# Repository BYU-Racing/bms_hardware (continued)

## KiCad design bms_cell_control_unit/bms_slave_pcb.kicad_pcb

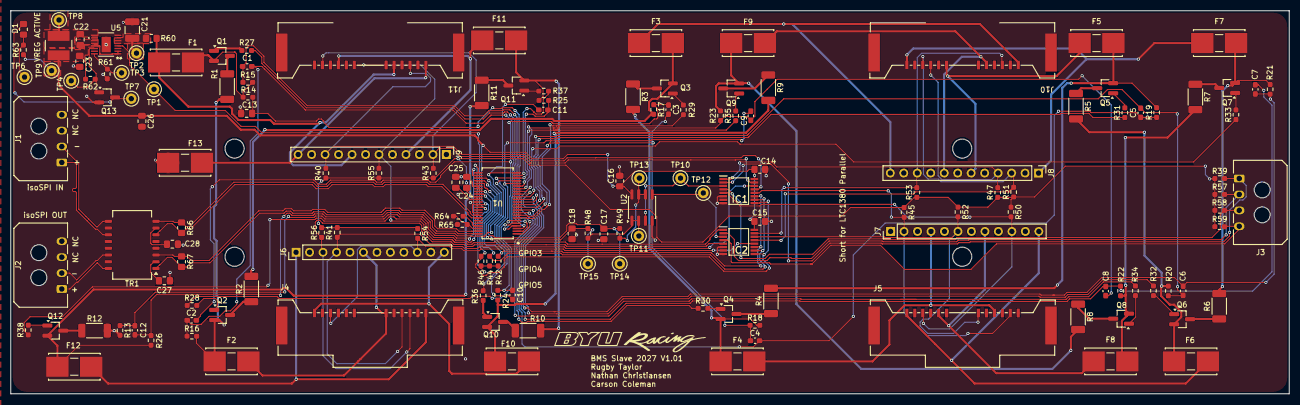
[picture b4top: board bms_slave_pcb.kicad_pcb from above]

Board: 2 copper layers, 241.0 x 72.2 mm, 152 parts (0 on the bottom side), 124 nets.

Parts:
C1, C2, C3, C4, C5, C6, C7, C8, C9, C10, C11, C12: 10nF; C_0603_1608Metric_Pad1.08x0.95mm_HandSolder
C13: 100nF; C_0805_2012Metric_Pad1.18x1.45mm_HandSolder
C14: 1uF; R_0805_2012Metric_Pad1.20x1.40mm_HandSolder
C15, C16: 1uf; R_0805_2012Metric_Pad1.20x1.40mm_HandSolder
C17, C18: 10nF; R_0805_2012Metric_Pad1.20x1.40mm_HandSolder
C21: 2.2uF; C_1210_3225Metric_Pad1.33x2.70mm_HandSolder
C22, C23: 22uF; C_0805_2012Metric_Pad1.18x1.45mm_HandSolder
C24, C25, C26: 1uF; C_0805_2012Metric_Pad1.18x1.45mm_HandSolder
C27, C28: 10nF; C_0805_2012Metric_Pad1.18x1.45mm_HandSolder
D1: LED; R_0805_2012Metric_Pad1.20x1.40mm_HandSolder
F1, F13: 500mA; Littelfuse_01550900M_Fuse_Blok_Cartridge
F2, F3, F4, F5, F6, F7, F8, F9, F10, F11, F12: 250mA; Littelfuse_01550900M_Fuse_Blok_Cartridge
IC1, IC2: TMUX1308AQPWRQ1; SOP65P640X120-16N
J1: isoSPI Daisy Chain IN; Molex_Micro-Fit_3.0_43650-0400_1x04_P3.00mm_Horizontal
J2: isoSPI Daisy Chain OUT; Molex_Micro-Fit_3.0_43650-0400_1x04_P3.00mm_Horizontal
J3: Extra Thermistor Connector; Molex_Micro-Fit_3.0_43650-0400_1x04_P3.00mm_Horizontal
J4: Module Top Left FPC Female; FPC_Female_Connector
J5: Module Top Right FPC Female; FPC_Female_Connector
J6, J7, J8, J9: Breadboard pins for testing; PinHeader_1x12_P2.54mm_Vertical
J10: Module Bottom Left FPC Female; FPC_Female_Connector
J11: Module Bottom Right FPC Female; FPC_Female_Connector
L1: 33uH; IND_LQH5BPH330MT0L
Q1, Q2, Q3, Q4, Q5, Q6, Q7, Q8, Q9, Q10, Q11, Q12: BSS308PE; SOT-23_Handsoldering
Q13: 2N7002; SOT-23_Handsoldering
R1, R2, R3, R4, R5, R6, R7, R8, R9, R10, R11, R12: 33; R_2010_5025Metric_Pad1.40x2.65mm_HandSolder
R13, R14, R15, R16, R17, R18, R19, R20, R21, R22, R23, R24, R25, R26, R48, R49: 100; R_0603_1608Metric_Pad0.98x0.95mm_HandSolder
R27, R28, R29, R30, R31, R32, R33, R34, R35, R36, R37, R38: 3.3k; R_0603_1608Metric_Pad0.98x0.95mm_HandSolder
R39, R40, R41, R43, R45, R47, R50, R51, R52, R53, R54, R55, R56, R57, R58, R59: 10k; R_0603_1608Metric_Pad0.98x0.95mm_HandSolder
R42, R44, R46: 4.7K; R_0603_1608Metric_Pad0.98x0.95mm_HandSolder
R60: 470; R_0805_2012Metric_Pad1.20x1.40mm_HandSolder
R61: 374k; R_0603_1608Metric_Pad0.98x0.95mm_HandSolder
R62: 220k; R_0603_1608Metric_Pad0.98x0.95mm_HandSolder
R63: 2.2k; R_0603_1608Metric_Pad0.98x0.95mm_HandSolder
R64, R65: 1k; R_0603_1608Metric_Pad0.98x0.95mm_HandSolder
R66, R67: 100; R_0805_2012Metric_Pad1.20x1.40mm_HandSolder
TP1, TP2, TP3, TP4, TP6, TP7, TP8, TP9, TP10, TP11, TP12, TP13, TP14, TP15: TestPoint; TestPoint_Keystone_5000-5004_Miniature
TR1: TG110I-AE050N5xx; Transformer_Ethernet_Halo_N5_SO-16_7.11x12.7mm
U1: LTC6811HGI-1I-3ZZTRPBF; 05-08-1887_ADI
U2: TLV9002IDR; SOIC-8_3.9x4.9mm_P1.27mm
U5: LT3990HMSEI-5I-PBF; MSOP-16_MSE_LIT

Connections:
/FPC Connections/TH1: IC1.13 (S0), J9.10, J11.10, R40.2
/FPC Connections/TH2: IC1.14 (S1), J4.4, J6.4, R41.2
/FPC Connections/TH3: IC1.15 (S2), J9.2, J11.2, R43.2
/FPC Connections/TH4: IC1.12 (S3), J5.2, J7.2, R45.2
/FPC Connections/TH5: IC1.1 (S4), J8.4, J10.4, R47.2
/FPC Connections/TH6: IC1.5 (S5), J5.10, J7.10, R50.2
/FPC Connections/TH7: IC2.13 (S0), J8.3, J10.3, R51.2
/FPC Connections/TH8: IC2.14 (S1), J5.6, J7.6, R52.2
/FPC Connections/TH9: IC2.15 (S2), J8.10, J10.10, R53.2
/FPC Connections/TH10: IC2.12 (S3), J4.10, J6.10, R54.2
/FPC Connections/TH11: IC2.1 (S4), J9.6, J11.6, R55.2
/FPC Connections/TH12: IC2.5 (S5), J4.3, J6.3, R56.2
/FPC Connections/VBUS1: F12.1, J4.1, J6.1
/FPC Connections/VBUS2: F11.1, J9.4, J11.4
/FPC Connections/VBUS3: F10.1, J4.12, J6.12
/FPC Connections/VBUS4: F9.1, J8.8, J10.8
/FPC Connections/VBUS5: F8.1, J5.8, J7.8
/FPC Connections/VBUS6: F7.1, J8.1, J10.1
/FPC Connections/VBUS7: F6.1, J5.12, J7.12
/FPC Connections/VBUS8: F5.1, J8.6, J10.6
/FPC Connections/VBUS9: F4.1, J5.4, J7.4
/FPC Connections/VBUS10: F3.1, J8.12, J10.12
/FPC Connections/VBUS11: F2.1, J4.6, J6.6
/FPC Connections/VBUS12: F1.1, J9.8, J11.8, R60.2
/FPC Connections/VBUS_GNDREF: F13.1, J9.12, J11.12
/Power Rail/DRIVE: TP1.1 (1_1), U1.38 (DRIVE), U5.4 (EN/UVLO)
/Power Rail/VREG: C14.1, C15.1, C16.1, C23.1, C26.1, IC1.16 (VDD), IC2.16 (VDD), L1.2, R42.1, R44.1, R46.1, R62.1, R63.1, TP9.1 (1_1), U1.37 (VREG), U1.40 (ISOMD), U2.8 (V+), U5.1 (FB/VOUT), U5.2 (FB/VOUT), U5.13 (BD)
/Temperature Sensing/GPIO1(MUX_OUT_1): C18.1, R48.1, TP15.1 (1_1), U1.27 (GPIO1)
/Temperature Sensing/GPIO2(MUX_OUT_2): C17.1, R49.1, TP14.1 (1_1), U1.28 (GPIO2)
/Temperature Sensing/GPIO3: IC1.11 (A0), IC2.11 (A0), R42.2, U1.29 (GPIO3)
/Temperature Sensing/GPIO4: IC1.10 (A1), IC2.10 (A1), R44.2, U1.32 (GPIO4)
/Temperature Sensing/GPIO5: IC1.9 (A2), IC2.9 (A2), R46.2, U1.33 (GPIO5)
/Temperature Sensing/TH0: IC1.2 (S6), J3.1, R39.2
/Temperature Sensing/TH13: IC2.2 (S6), J3.2, R57.2
/Temperature Sensing/TH14: IC1.4 (S7), J3.3, R58.2
/Temperature Sensing/TH15: IC2.4 (S7), J3.4, R59.2
/Temperature Sensing/V_REF2: C24.1, R39.1, R40.1, R41.1, R43.1, R45.1, R47.1, R50.1, R51.1, R52.1, R53.1, R54.1, R55.1, R56.1, R57.1, R58.1, R59.1, U1.34 (VREF2)
/Voltage Taps/C0: C12.2, R13.1, U1.26 (C0)
/Voltage Taps/C1: C11.2, C12.1, R26.1, U1.24 (C1)
/Voltage Taps/C2: C10.2, C11.1, R25.1, U1.22 (C2)
/Voltage Taps/C3: C9.2, C10.1, R24.1, U1.20 (C3)
/Voltage Taps/C4: C8.2, C9.1, R23.1, U1.18 (C4)
/Voltage Taps/C5: C7.2, C8.1, R22.1, U1.16 (C5)
/Voltage Taps/C6: C6.2, C7.1, R21.1, U1.14 (C6)
/Voltage Taps/C7: C5.2, C6.1, R20.1, U1.12 (C7)
/Voltage Taps/C8: C4.2, C5.1, R19.1, U1.10 (C8)
/Voltage Taps/C9: C3.2, C4.1, R18.1, U1.8 (C9)
/Voltage Taps/C10: C2.2, C3.1, R17.1, U1.6 (C10)
/Voltage Taps/C11: C1.2, C2.1, R16.1, U1.4 (C11)
/Voltage Taps/C12: C1.1, R15.1, U1.2 (C12)
/Voltage Taps/S1: R38.1, U1.25 (S1)
/Voltage Taps/S2: R37.1, U1.23 (S2)
/Voltage Taps/S3: R36.1, U1.21 (S3)
/Voltage Taps/S4: R35.1, U1.19 (S4)
/Voltage Taps/S5: R34.1, U1.17 (S5)
/Voltage Taps/S6: R33.1, U1.15 (S6)
/Voltage Taps/S7: R32.1, U1.13 (S7)
/Voltage Taps/S8: R31.1, U1.11 (S8)
/Voltage Taps/S9: R30.1, U1.9 (S9)
/Voltage Taps/S10: R29.1, U1.7 (S10)
/Voltage Taps/S11: R28.1, U1.5 (S11)
/Voltage Taps/S12: R27.1, U1.3 (S12)
/Voltage Taps/VI+: C13.1, R14.1, U1.1 (V+)
/isoSPI Daisy Chain/+: R66.2, TR1.6 (RX-), U1.42 (SCK(IPA))
/isoSPI Daisy Chain/-: R66.1, TR1.8 (RX+), U1.41 (CSB(IMA))
/isoSPI Daisy Chain/I+: R67.2, TR1.1 (TX-), U1.48 (IPB)
/isoSPI Daisy Chain/I-: R67.1, TR1.3 (TX+), U1.47 (IMB)
/isoSPI Daisy Chain/IBIAS: R64.2, U1.45 (IBIAS)
/isoSPI Daisy Chain/ICMP: R64.1, R65.2, U1.46 (ICMP)
/isoSPI Daisy Chain/V_REF1: C25.1, U1.35 (VREF1)
/isoSPI Daisy Chain/isoSPIAI+: J1.1, TR1.11 (RD-)
/isoSPI Daisy Chain/isoSPIAI-: J1.2, TR1.9 (RD+)
/isoSPI Daisy Chain/isoSPIBI+: J2.1, TR1.16 (TD-)
/isoSPI Daisy Chain/isoSPIBI-: J2.2, TR1.14 (TD+)
GNDREF: C13.2, C14.2, C15.2, C16.2, C17.2, C18.2, C21.2, C23.2, C24.2, C25.2, C26.2, C27.2, C28.2, F13.2, IC1.6 (~EN), IC1.8 (GND), IC2.6 (~EN), IC2.8 (GND), J4.2, J4.5, J4.7, J4.9, J4.11, J5.1, J5.3, J5.5, J5.7, J5.9, J5.11, J6.2, J6.5, J6.7, J6.9, J6.11, J7.1, J7.3, J7.5, J7.7, J7.9, J7.11, J8.2, J8.5, J8.7, J8.9, J8.11, J9.1, J9.3, J9.5, J9.7, J9.9, J9.11, J10.2, J10.5, J10.7, J10.9, J10.11, J11.1, J11.3, J11.5, J11.7, J11.9, J11.11, Q13.2 (S), R12.2, R13.2, R61.2, R65.1, U1.30 (V-), U1.31 (V-), U1.36 (DTEN), U2.4 (V-), U5.8 (GND), U5.17
unnamed: D1.2 (A), R63.2, TP6.1 (1_1)
unnamed: D1.1 (K), Q13.3 (D), TP7.1 (1_1)
unnamed: IC1.3 (D), TP10.1 (1_1), U2.3
unnamed: IC2.3 (D), TP12.1 (1_1), U2.5
unnamed: Q1.3 (D), R1.1
unnamed: Q1.1 (G), R27.2
unnamed: F1.2, Q1.2 (S), R14.2, R15.2
unnamed: Q2.3 (D), R2.1
unnamed: Q2.1 (G), R28.2
unnamed: F2.2, Q2.2 (S), R1.2, R16.2
unnamed: Q3.3 (D), R3.1
unnamed: Q3.1 (G), R29.2
unnamed: F3.2, Q3.2 (S), R2.2, R17.2
unnamed: Q4.3 (D), R4.1
unnamed: Q4.1 (G), R30.2
unnamed: F4.2, Q4.2 (S), R3.2, R18.2
unnamed: Q5.3 (D), R5.1
unnamed: Q5.1 (G), R31.2
unnamed: F5.2, Q5.2 (S), R4.2, R19.2
unnamed: Q6.3 (D), R6.1
unnamed: Q6.1 (G), R32.2
unnamed: F6.2, Q6.2 (S), R5.2, R20.2
unnamed: Q7.3 (D), R7.1
unnamed: Q7.1 (G), R33.2
unnamed: F7.2, Q7.2 (S), R6.2, R21.2
unnamed: Q8.3 (D), R8.1
unnamed: Q8.1 (G), R34.2
unnamed: F8.2, Q8.2 (S), R7.2, R22.2
unnamed: Q9.3 (D), R9.1
unnamed: Q9.1 (G), R35.2
unnamed: F9.2, Q9.2 (S), R8.2, R23.2
unnamed: Q10.3 (D), R10.1
unnamed: Q10.1 (G), R36.2
unnamed: F10.2, Q10.2 (S), R9.2, R24.2
unnamed: Q11.3 (D), R11.1
unnamed: Q11.1 (G), R37.2
unnamed: F11.2, Q11.2 (S), R10.2, R25.2
unnamed: Q12.3 (D), R12.1
unnamed: Q12.1 (G), R38.2
unnamed: F12.2, Q12.2 (S), R11.2, R26.2
unnamed: Q13.1 (G), R62.2, TP4.1 (1_1), U5.14 (PG)
unnamed: R48.2, TP11.1 (1_1), U2.1, U2.2
unnamed: R49.2, TP13.1 (1_1), U2.6, U2.7
unnamed: C28.1, TR1.7 (C_RX)
unnamed: C27.1, TR1.2 (C_TX)
unnamed: C22.1, U5.11 (BOOST)
unnamed: R61.1, TP3.1 (1_1), U5.16 (RT)
unnamed: C22.2, L1.1, TP8.1 (1_1), U5.9 (SW)
unnamed: C21.1, R60.1, TP2.1 (1_1), U5.6 (VIN)

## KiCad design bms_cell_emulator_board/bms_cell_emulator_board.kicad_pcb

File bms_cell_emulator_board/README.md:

# BMS Cell Emulator V1
These are the KiCad PCB files relating to Nathan Christiansen's V1 for a PCB designed to emulate 
the battery cells of an individual module. With something similar to this we can test the Cell Monitor PCBs 
and the Main Control Unit for the BMS without the need to plug those PCBs into the battery first. We can
safely test those different parts of the BMS before we plug them into live battery cells.

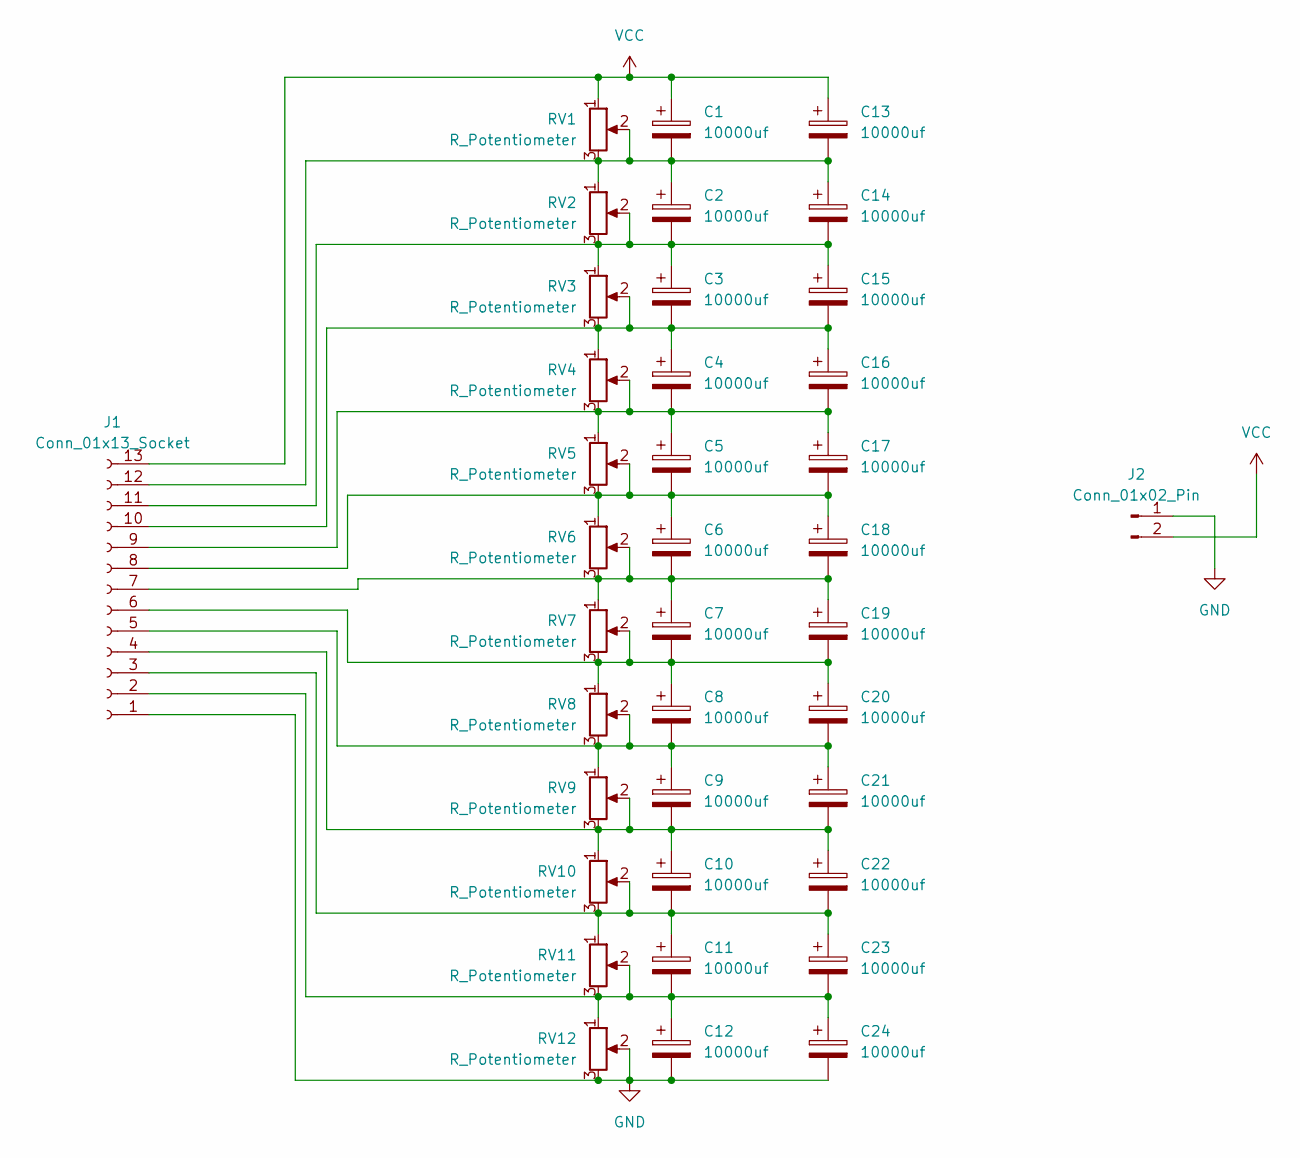
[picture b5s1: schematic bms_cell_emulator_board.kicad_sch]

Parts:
C1, C2, C3, C4, C5, C6, C7, C8, C9, C10, C11, C12, C13, C14, C15, C16, C17, C18, C19, C20, C21, C22, C23, C24: 10000uf; CP_Radial_D16.0mm_P7.50mm
J1: Conn_01x13_Socket; PinHeader_1x13_P2.54mm_Vertical
J2: Conn_01x02_Pin; AMASS_XT30U-M_1x02_P5.0mm_Vertical
RV1, RV2, RV3, RV4, RV5, RV6, RV7, RV8, RV9, RV10, RV11, RV12: R_Potentiometer; Potentiometer_Bourns_3386W_Horizontal

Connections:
GND: C12.2, C24.2, J1.1, J2.1, RV12.2, RV12.3
unnamed: C11.2, C12.1, C23.2, C24.1, J1.2, RV11.2, RV11.3, RV12.1
unnamed: C10.2, C11.1, C22.2, C23.1, J1.3, RV10.2, RV10.3, RV11.1
unnamed: C9.2, C10.1, C21.2, C22.1, J1.4, RV9.2, RV9.3, RV10.1
unnamed: C8.2, C9.1, C20.2, C21.1, J1.5, RV8.2, RV8.3, RV9.1
unnamed: C7.2, C8.1, C19.2, C20.1, J1.6, RV7.2, RV7.3, RV8.1
unnamed: C6.2, C7.1, C18.2, C19.1, J1.7, RV6.2, RV6.3, RV7.1
unnamed: C5.2, C6.1, C17.2, C18.1, J1.8, RV5.2, RV5.3, RV6.1
unnamed: C4.2, C5.1, C16.2, C17.1, J1.9, RV4.2, RV4.3, RV5.1
unnamed: C3.2, C4.1, C15.2, C16.1, J1.10, RV3.2, RV3.3, RV4.1
unnamed: C2.2, C3.1, C14.2, C15.1, J1.11, RV2.2, RV2.3, RV3.1
unnamed: C1.2, C2.1, C13.2, C14.1, J1.12, RV1.2, RV1.3, RV2.1
VCC: C1.1, C13.1, J1.13, J2.2, RV1.1

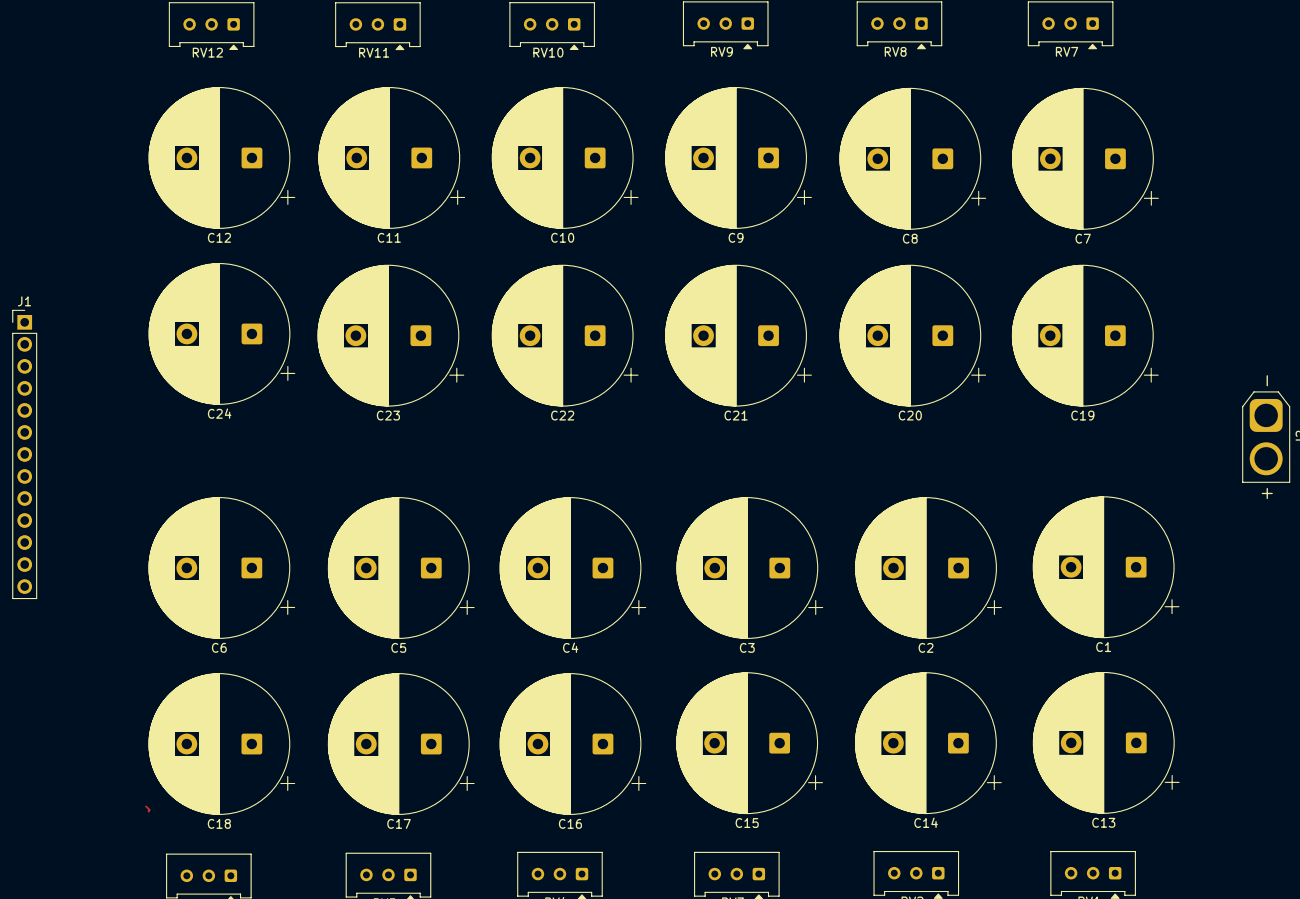
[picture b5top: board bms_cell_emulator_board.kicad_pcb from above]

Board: 2 copper layers, 38 parts (0 on the bottom side), 13 nets.

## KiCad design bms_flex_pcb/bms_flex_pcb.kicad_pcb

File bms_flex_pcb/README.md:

# BMS Flex PCBs (FPCs) V1 Files

This was originally intended to be used as the connection from the current collector plates on the modules to the
BMS Cell Monitor PCB V1.01. (the FSAE rules calls this connection the "Voltage sense leads")

The idea to use the FPCs was scrapped for the 2027 season in late October of 2026 due to team integration timeline constraints. We defaulted back to using the long leads off the current collector plates.
This is still a totally viable and incredibly sleek solution for future years (many other FSAE teams use this and EV companies are beginning to move towards a solution similar to this)

The main intent behind using these was as follows:
- instead of using very long tabs on the current collector plates we can solder these very close to the cell stack,
eliminating a lot of risk while manufacturing (because with the long collector plate tabs we have a risk of shorting those tabs to neighboring cells)
- We can have the thermistors soldered directly to the FPC and thus have a closer and better thermal connection to the cells
- Another ease of manufacturing is that we can just lay this across the cells and then solder it and its done.

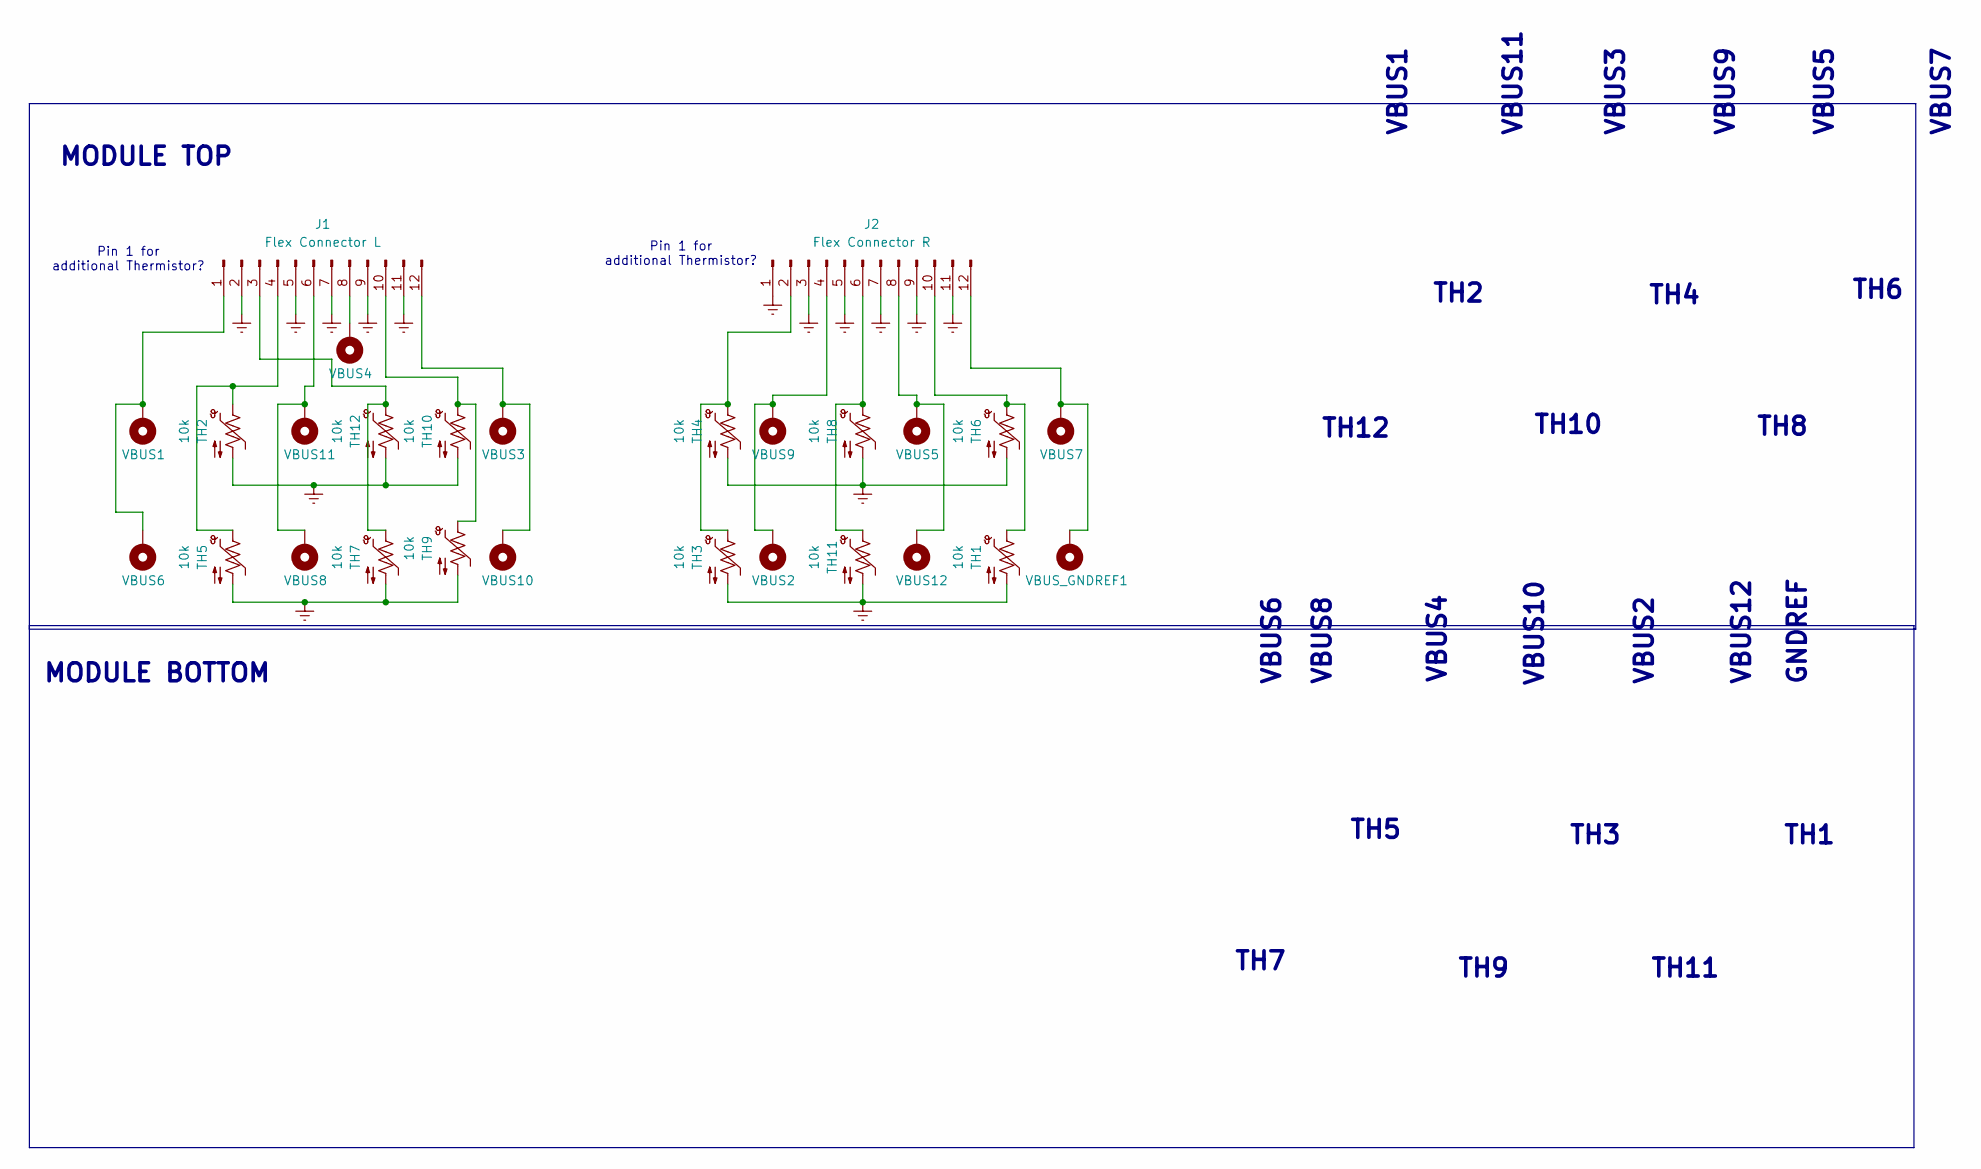
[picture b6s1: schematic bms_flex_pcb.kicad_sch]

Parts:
J1: Flex Connector L; Molex_2190190120_FPC_Board_Connect
J2: Flex Connector R; Molex_2190190120_FPC_Board_Connect
TH1, TH2, TH3, TH4, TH5, TH6, TH7, TH8, TH9, TH10, TH11, TH12: 10k; R_0603_1608Metric_Pad0.98x0.95mm_HandSolder
VBUS1, VBUS2, VBUS3, VBUS4, VBUS5, VBUS6, VBUS7, VBUS8, VBUS9, VBUS10, VBUS11, VBUS12: MountingHole_Pad; 2026_BMS_Voltage_Tap
VBUS_GNDREF1: MountingHole_Pad; 2026_BMS_Voltage_Tap

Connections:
GNDREF: J1.2, J1.5, J1.7, J1.9, J1.11, J2.1, J2.3, J2.5, J2.7, J2.9, J2.11, TH1.2, TH2.2, TH3.2, TH4.2, TH5.2, TH6.2, TH7.2, TH8.2, TH9.2, TH10.2, TH11.2, TH12.2
unnamed: J1.1, VBUS1.1 (1_1), VBUS6.1 (1_1)
unnamed: J1.3, TH7.1, TH12.1
unnamed: J1.4, TH2.1, TH5.1
unnamed: J1.6, VBUS8.1 (1_1), VBUS11.1 (1_1)
unnamed: J1.8, VBUS4.1 (1_1)
unnamed: J1.10, TH9.1, TH10.1
unnamed: J1.12, VBUS3.1 (1_1), VBUS10.1 (1_1)
unnamed: J2.2, TH3.1, TH4.1
unnamed: J2.4, VBUS2.1 (1_1), VBUS9.1 (1_1)
unnamed: J2.6, TH8.1, TH11.1
unnamed: J2.8, VBUS5.1 (1_1), VBUS12.1 (1_1)
unnamed: J2.10, TH1.1, TH6.1
unnamed 13: J2.12, VBUS7.1 (1_1), VBUS_GNDREF1.1; also elsewhere on the board

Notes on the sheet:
GNDREF
TH12
TH7
TH10
MODULE BOTTOM
TH2
VBUS3
VBUS12
VBUS10
TH6
MODULE TOP
Pin 1 for additional Thermistor?
VBUS5
VBUS11
VBUS9
TH8
TH5
TH4
VBUS7
VBUS1
VBUS8
VBUS6
TH3
TH11
VBUS4
TH1
VBUS2
TH9

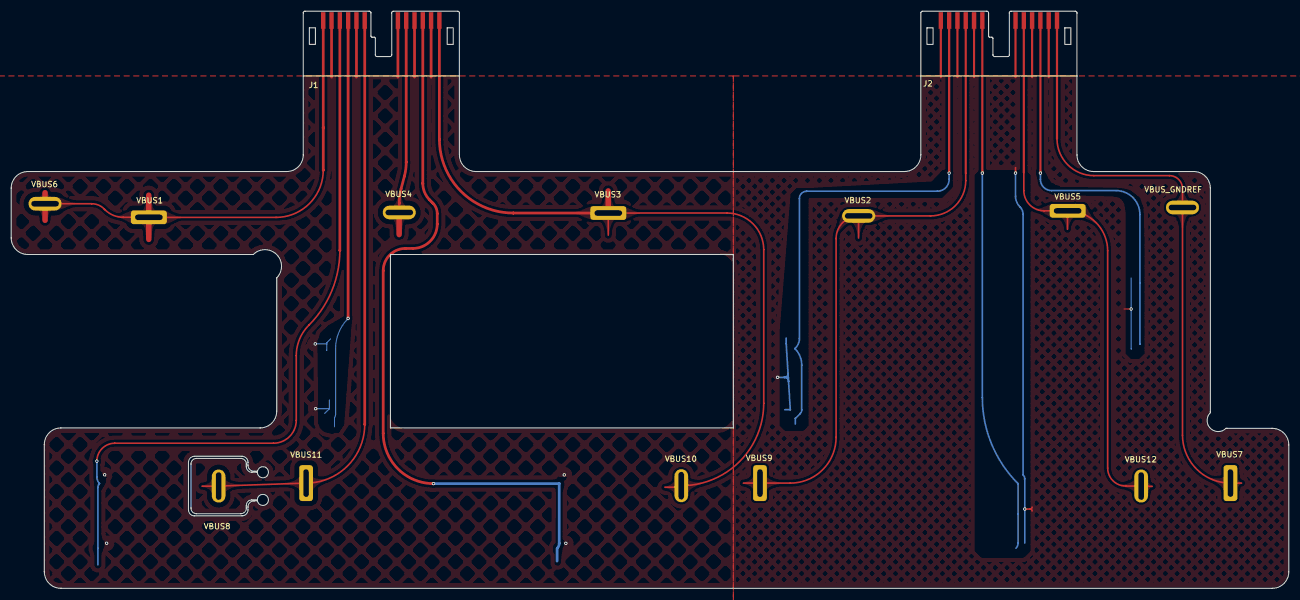
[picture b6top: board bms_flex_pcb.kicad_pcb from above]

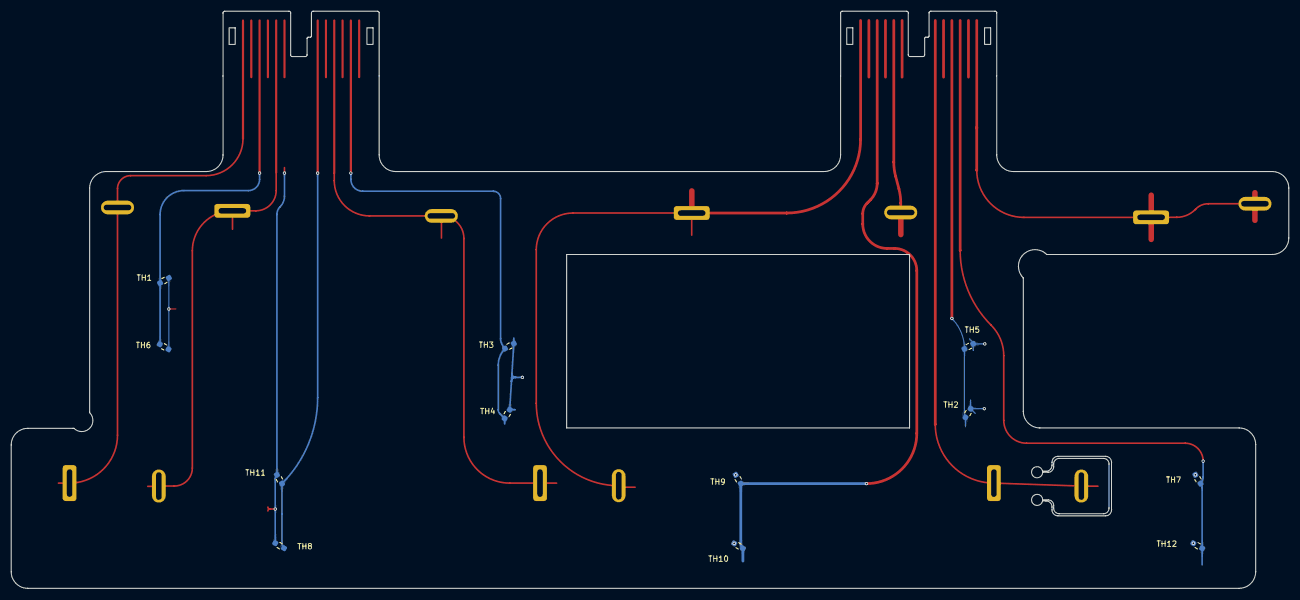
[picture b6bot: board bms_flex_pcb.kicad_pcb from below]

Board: 2 copper layers, 231.0 x 104.3 mm, 27 parts (12 on the bottom side), 14 nets.

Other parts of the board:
VBUS_GNDREF: MountingHole_Pad; 2026_BMS_Voltage_Tap

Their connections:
unnamed 13: VBUS_GNDREF.1 (1_1); also elsewhere on the board

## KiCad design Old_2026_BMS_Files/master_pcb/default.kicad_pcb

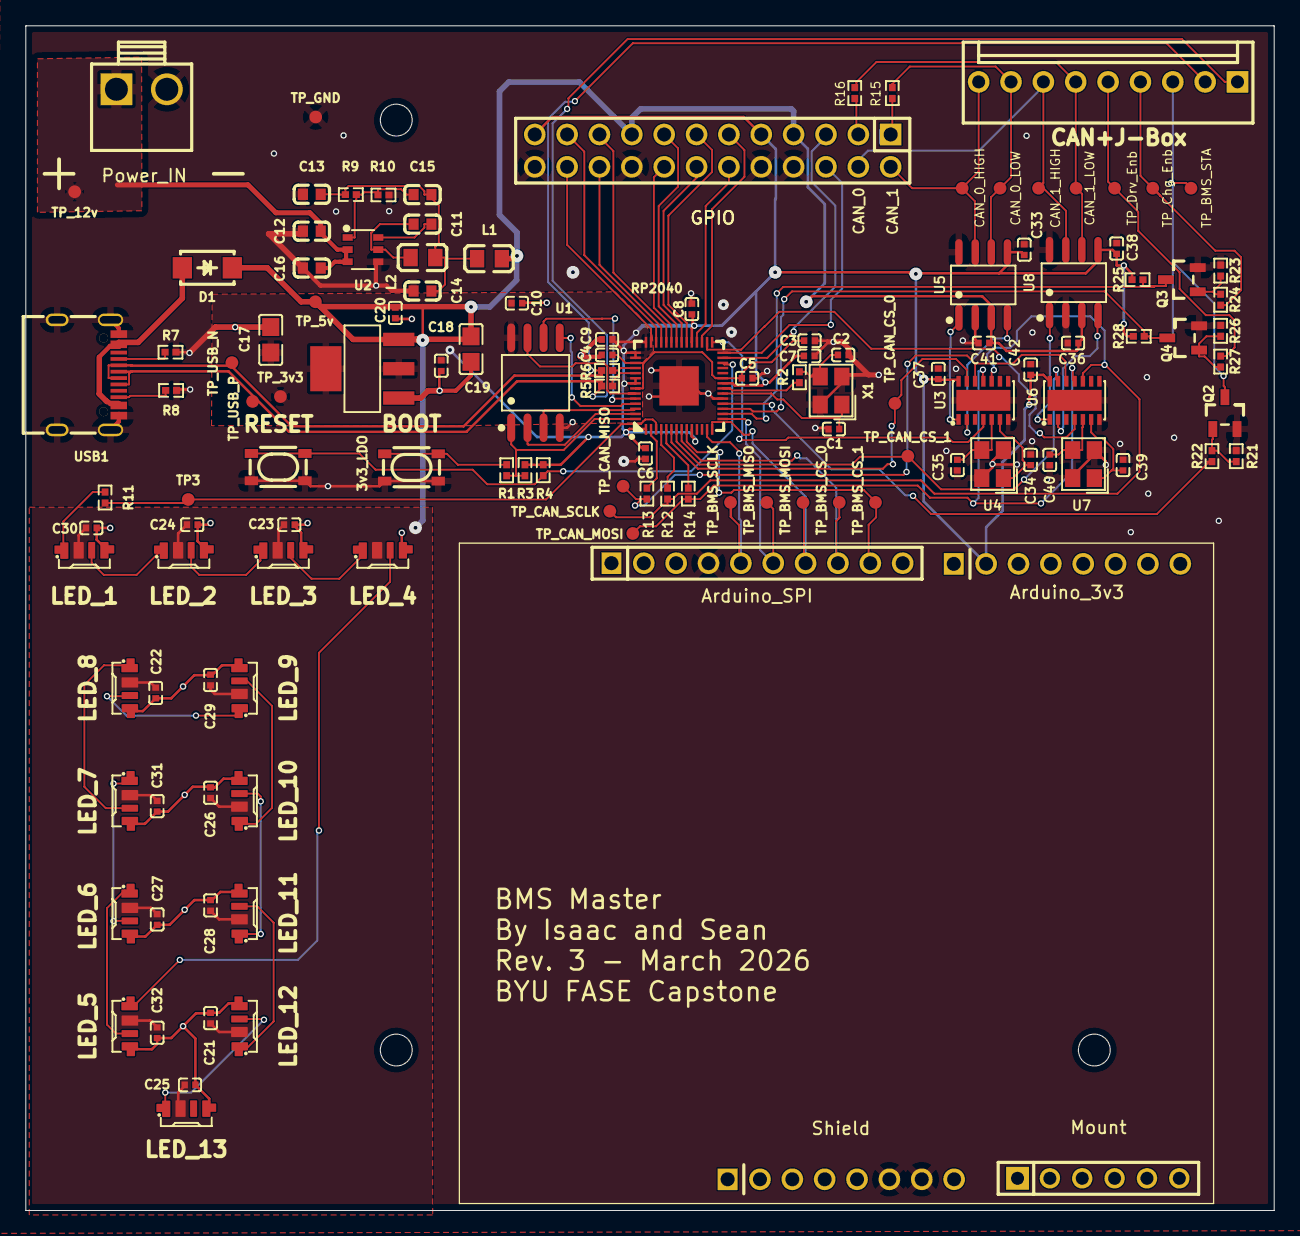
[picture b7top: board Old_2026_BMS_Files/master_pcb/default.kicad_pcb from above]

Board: 2 copper layers, 98.0 x 93.0 mm, 130 parts (0 on the bottom side), 91 nets.

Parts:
3v3_LDO: SOT-223_L6.5-W3.5-P2.30-LS7.0-BR
Arduino_3v3: HDR-TH_8P-P2.54-V-F
Arduino_SPI: HDR-TH_10P-P2.54-V-F
BOOT: KEY-SMD_4P-L4.2-W3.2-P2.20-LS4.6
C1, C2, C34, C35, C39, C40: 22pF ±5% 50V C0G; C0402
C3, C4, C5, C6, C7, C8, C9, C10: 1µF ±10% 25V X5R; C0402
C11, C16: 100nF ±10% 50V X7R; C0603
C12: 10µF ±10% 10V X5R; C0603
C13, C14: 22µF ±20% 6.3V X5R; C0603
C15: 47pF ±5% 50V C0G; C0603
C17, C19: 10µF ±10% 25V X5R; C0805
C18, C20, C21, C22, C23, C24, C25, C26, C27, C28, C29, C30, C31, C32, C33, C36, C37, C38, C41, C42: 100nF ±10% 16V X7R; C0402
CAN+J-Box: CONN-TH_9P-P2.54_MOLEX_22232091
CAN_0_HIGH, CAN_0_LOW, CAN_1_HIGH, CAN_1_LOW: TestPoint_Pad_D1.0mm
D1: SMA_L4.2-W2.6-LS5.0-RD_1
GPIO: HDR-TH_24P-P2.54-V-M-R2-C12-S2.54
L1: L0805
L2: 6.8µH ±20% 550mA 270mΩ; L0805
LED_1, LED_2, LED_3, LED_4, LED_5, LED_6, LED_7, LED_8, LED_9, LED_10, LED_11, LED_12, LED_13: LED-SMD_4P-L4.0-W1.6-L
Mount: HDR-TH_6P-P2.54-V-F
Power_IN: CONN-TH_B2P-VH-LF-SN
Q2, Q3, Q4: SOT-23-3_L2.9-W1.3-P1.90-LS2.4-TR
R1, R2: 1kΩ ±1% 62.5mW; R0402
R3, R4, R25, R28: 10kΩ ±1% 62.5mW; R0402
R5, R6: 27Ω ±1% 62.5mW; R0402
R7, R8, R22: 4.7kΩ ±1% 62.5mW; R0402
R9: 158kΩ ±1% 62.5mW; R0402
R10: 30.1kΩ ±1% 62.5mW; R0402
R11: 150Ω ±1% 62.5mW; R0402
R12, R13, R14: 22Ω ±1% 62.5mW; R0402
R15, R16: 120Ω ±1% 62.5mW; R0402
R21, R24, R27: 100kΩ ±1% 62.5mW; R0402
R23, R26: 1MΩ ±1% 62.5mW; R0402
RESET: KEY-SMD_4P-L4.2-W3.2-P2.20-LS4.6
RP2040: LQFN-56_L7.0-W7.0-P0.4-EP
Shield: HDR-TH_8P-P2.54-V-F
TP3: TestPoint_Pad_D1.0mm
TP_3v3, TP_5v, TP_12v: TestPoint_Pad_D1.0mm
TP_BMS_CS_0, TP_BMS_CS_1: TestPoint_Pad_D1.0mm
TP_BMS_MISO: TestPoint_Pad_D1.0mm
TP_BMS_MOSI: TestPoint_Pad_D1.0mm
TP_BMS_SCLK: TestPoint_Pad_D1.0mm
TP_BMS_STA: TestPoint_Pad_D1.0mm
TP_CAN_CS_0, TP_CAN_CS_1: TestPoint_Pad_D1.0mm
TP_CAN_MISO: TestPoint_Pad_D1.0mm
TP_CAN_MOSI: TestPoint_Pad_D1.0mm
TP_CAN_SCLK: TestPoint_Pad_D1.0mm
TP_Chg_Enb: TestPoint_Pad_D1.0mm
TP_Drv_Enb: TestPoint_Pad_D1.0mm
TP_GND: TestPoint_Pad_D1.0mm
TP_USB_N: TestPoint_Pad_D1.0mm
TP_USB_P: TestPoint_Pad_D1.0mm
U1: SOIC-8_L5.3-W5.3-P1.27-LS8.0-BL
U2: TSOT-23-6_L2.9-W1.6-P0.95-LS2.8-BR
U3, U6: VDFN-14_L4.5-W3.0-P0.65-BL-EP
U4, U7: CRYSTAL-SMD_4P-L3.2-W2.5-BL
U5, U8: SOIC-8_L4.9-W3.9-P1.27-LS6.0-BL
USB1: USB-C-SMD_KH-TYPE-C-16P
X1: CRYSTAL-SMD_4P-L3.2-W2.5-BL

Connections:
3V: 3v3_LDO.2, 3v3_LDO.4, Arduino_3v3.2, C6.1, C7.1, C8.1, C9.1, C10.1, C17.1, C18.1, C33.1, C37.1, C38.1, C42.1, GPIO.9, GPIO.23, R3.1, R4.1, R25.1, R28.1, RP2040.1, RP2040.10, RP2040.22, RP2040.33, RP2040.42, RP2040.43, RP2040.44, RP2040.48, RP2040.49, TP_3v3.1, U1.8, U3.14, U5.5, U6.14, U8.5
5V: 3v3_LDO.3, C19.1, C20.1, C21.1, C22.1, C23.1, C24.1, C25.1, C26.1, C27.1, C28.1, C29.1, C30.1, C31.1, C32.1, C36.1, C41.1, D1.1, GPIO.7, GPIO.17, L1.2, LED_1.2, LED_2.2, LED_3.2, LED_4.2, LED_5.2, LED_6.2, LED_7.2, LED_8.2, LED_9.2, LED_10.2, LED_11.2, LED_12.2, LED_13.2, TP_5v.1, U5.3, U8.3
12V: C12.1, C16.1, Power_IN.1, TP_12v.1, U2.2, U2.3
A5: R7.1, USB1.A5
B5: R8.1, USB1.B5
BMS_status: CAN+J-Box.3, Q2.3, TP_BMS_STA.1
BST: C11.1, U2.6
CAN_CS_0: RP2040.6, TP_CAN_CS_0.1, U3.13
CAN_CS_1: RP2040.7, TP_CAN_CS_1.1, U6.13
FB: C15.2, R9.2, R10.1, U2.1
GND: 3v3_LDO.1, Arduino_SPI.4, BOOT.1, BOOT.2, C1.2, C2.2, C3.2, C4.2, C5.2, C6.2, C7.2, C8.2, C9.2, C10.2, C12.2, C13.2, C14.2, C16.2, C17.2, C18.2, C19.2, C20.2, C21.2, C22.2, C23.2, C24.2, C25.2, C26.2, C27.2, C28.2, C29.2, C30.2, C31.2, C32.2, C33.2, C34.2, C35.2, C36.2, C37.2, C38.2, C39.2, C40.2, C41.2, C42.2, GPIO.8, GPIO.10, GPIO.18, GPIO.24, LED_1.4, LED_2.4, LED_3.4, LED_4.4, LED_5.4, LED_6.4, LED_7.4, LED_8.4, LED_9.4, LED_10.4, LED_11.4, LED_12.4, LED_13.4, Power_IN.2, Q2.1, Q3.1, Q4.1, R7.2, R8.2, R10.2, R21.2, R23.2, R26.2, RESET.1, RESET.2, RP2040.19, RP2040.57, Shield.6, Shield.7, TP_GND.1, U1.4, U2.4, U3.7, U3.15, U4.2, U4.4, U5.2, U5.8, U6.7, U6.15, U7.2, U7.4, U8.2, U8.8, USB1.1, USB1.2, USB1.3, USB1.4, USB1.A1, USB1.A12, USB1.B1, USB1.B12, X1.2, X1.4
RX: GPIO.6, RP2040.28
SCL: GPIO.12, RP2040.32
SDA: GPIO.11, RP2040.31
SW: C11.2, L2.1, U2.5
TX: GPIO.5, RP2040.27
TestPoint_LED_DATA-contact: R11.1, RP2040.3, TP3.1
TestPoint_SPI1_CS_0-contact: Arduino_SPI.8, RP2040.8, TP_BMS_CS_0.1
TestPoint_SPI1_CS_1-contact: Arduino_SPI.9, RP2040.9, TP_BMS_CS_1.1
TestPoint_SPI1_MISO-contact: Arduino_SPI.6, RP2040.15, TP_BMS_MISO.1
USB_DM: R6.2, RP2040.46
USB_DP: R5.2, RP2040.47
USB_D_N: CAN+J-Box.2, R6.1, TP_USB_N.1, USB1.A7, USB1.B7
USB_D_P: CAN+J-Box.1, R5.1, TP_USB_P.1, USB1.A6, USB1.B6
XIN: C1.1, RP2040.20, X1.1
XOUT: R2.1, RP2040.21
bms_status_base_pulldown-B: Q2.2, R21.1, R22.2
boot_btn-output: BOOT.3, BOOT.4, R1.1
button-output: R4.2, RESET.3, RESET.4, RP2040.26
c_osc_2-OSC2: C2.1, R2.2, X1.3
can0-OSC1: C34.1, U3.6, U4.1
can0-OSC2: C35.1, U3.5, U4.3
can0-RXCAN: U3.2, U5.4
can0-TXCAN: U3.1, U5.1
can0-nint: RP2040.29, U3.4
can1-OSC1: C39.1, U6.6, U7.1
can1-OSC2: C40.1, U6.5, U7.3
can1-RXCAN: U6.2, U8.4
can1-TXCAN: U6.1, U8.1
can1-nint: RP2040.30, U6.4
can_0_high: CAN+J-Box.9, CAN_0_HIGH.1, GPIO.2, U5.7
can_0_low: CAN+J-Box.8, CAN_0_LOW.1, R15.2, U5.6
can_0_terminator-_1: GPIO.1, R15.1
can_1_high: CAN+J-Box.7, CAN_1_HIGH.1, GPIO.4, U8.7
can_1_low: CAN+J-Box.6, CAN_1_LOW.1, R16.2, U8.6
can_1_terminator-_3: GPIO.3, R16.1
charge_enable: CAN+J-Box.4, R24.1, TP_Chg_Enb.1
charge_enable_base_pulldown-B: Q3.2, R23.1, R24.2
charge_enable_pullup-C: Q3.3, R25.2, RP2040.16
cs: R1.2, R3.2, RP2040.56, U1.1
drive_enable: CAN+J-Box.5, R27.1, TP_Drv_Enb.1
drive_enable_base_pulldown-B: Q4.2, R26.1, R27.2
drive_enable_pullup-C: Q4.3, R28.2, RP2040.17
footprint-DIN-0: LED_1.1, R11.2
footprint-DIN-1: LED_1.3, LED_2.1
footprint-DIN-2: LED_10.3, LED_11.1
footprint-DIN-3: LED_11.3, LED_12.1
footprint-DIN-4: LED_12.3, LED_13.1
footprint-DIN-5: LED_2.3, LED_3.1
footprint-DIN-6: LED_3.3, LED_4.1
footprint-DIN-7: LED_4.3, LED_5.1
footprint-DIN-8: LED_5.3, LED_6.1
footprint-DIN-9: LED_6.3, LED_7.1
footprint-DIN-10: LED_7.3, LED_8.1
footprint-DIN-11: LED_8.3, LED_9.1
footprint-DIN-12: LED_9.3, LED_10.1
gpio0: R13.1, RP2040.2
gpio2: R12.1, RP2040.4
gpio3: R14.1, RP2040.5
gpio15: R22.1, RP2040.18
gpio22: GPIO.13, RP2040.34
gpio23: GPIO.14, RP2040.35
gpio24: GPIO.15, RP2040.36
gpio25: GPIO.16, RP2040.37
gpio26_a0: GPIO.19, RP2040.38
gpio27_a1: GPIO.20, RP2040.39
gpio28_a2: GPIO.21, RP2040.40
gpio29_a3: GPIO.22, RP2040.41
io0: RP2040.53, U1.5
io1: RP2040.55, U1.2
io2: RP2040.54, U1.3
io3: RP2040.51, U1.7
power_1V-VCC: C3.1, C4.1, C5.1, RP2040.23, RP2040.45, RP2040.50
sclk: RP2040.52, U1.6
spi1-MOSI: Arduino_SPI.7, RP2040.14, TP_BMS_MOSI.1
spi1-SCLK: Arduino_SPI.5, RP2040.13, TP_BMS_SCLK.1
spi-MISO: R13.2, TP_CAN_MISO.1, U3.12, U6.12
spi-MOSI: R14.2, TP_CAN_MOSI.1, U3.11, U6.11
spi-SCLK: R12.2, TP_CAN_SCLK.1, U3.10, U6.10
usb_vbus-VCC: D1.2, USB1.A4, USB1.A9, USB1.B4, USB1.B9
vout_sw-VCC: C13.1, C14.1, C15.1, L1.1, L2.2, R9.1
